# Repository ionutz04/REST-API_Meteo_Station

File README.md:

# 🌦️ SHT21 REST API - IoT Weather Monitoring Station

**Collaborators:** Ionescu Ionut

---

## 📝 General Description

This project implements a robust **IoT Weather Monitoring Station** designed for high-accuracy environmental data acquisition. The system is built around an **ESP32 microcontroller** running FreeRTOS (via ESP-IDF) and integrates with a local **NVIDIA Jetson Nano** gateway for data processing and storage.

### System Architecture
- **Edge Node (ESP32):** Collects sensor data via I²C, ADC, and Interrupt Service Routines (ISR).
- **Communication:** Secure HTTPS transmission (Ad-Hoc WiFi) to a Flask REST API.
- **Backend:** Redis TimeSeries database for high-speed storage.
- **Visualization:** Real-time Grafana dashboards.

### 🔑 Key Features
| Feature | Description |
| :--- | :--- |
| **Real-time Acquisition** | Low-latency polling of temperature, humidity, pressure, and wind metrics. |
| **Secure Transport** | JWT-authenticated HTTPS transmission between edge and gateway. |
| **Data Integrity** | Time-series storage with automatic aggregation and persistence. |
| **Visualization** | Custom Grafana dashboards for instant monitoring. |
| **Export Capability** | CSV data export for offline meteorological analysis. |

---

## 🧾 BOM (Bill Of Materials)

| # | Component | Quantity | Description | Interface/Notes |
|:-:|:---|:-:|:---|:---|
| 1 | **ESP32 DevKit** | 1 | ESP32-WROOM-32 Development Board | Main Controller |
| 2 | **SHT21** | 1 | Digital Temp & Humidity Sensor | I²C (0x40) |
| 3 | **MS5611** | 1 | Barometric Pressure Sensor | I²C |
| 4 | **GP2Y Series** | 1 | Optical Dust Sensor (e.g., GP2Y1014AU0F) | Analog + LED Pulse |
| 5 | **SparkFun Weather Meter** | 1 | [SEN-15901](https://www.sparkfun.com/products/15901) Kit | Wind/Rain Assembly |
| 6 | **10kΩ Resistors** | 2 | 1/4W Resistors | Voltage Divider (Wind Vane) |
| 7 | **Nvidia Jetson Nano** | 1 | Orin / 8GB Model | Gateway & ML Server |
| 8 | **Power Supply** | 1 | 5V DC Source | Reliable supply for ESP32 |
| 9 | **Enclosure** | 1 | IP65/Weatherproof Box | Outdoor deployment |

### 🔌 Sensor Pinout Configuration
| Sensor | Signal Type | ESP32 Pin | Logic |
| :--- | :--- | :--- | :--- |
| **Anemometer** | Digital (Pulse) | `GPIO32` | ISR (Falling Edge) |
| **Wind Vane** | Analog (ADC) | `GPIO36` | Voltage Divider Network |
| **Rain Gauge** | Digital (Pulse) | `GPIO33` | ISR (Debounced) |
| **GP2Y1014**| LED - Digital ; photodetector - Analog | `GPIO34` | The LED toggles on 20 $\mu s$ and the analog pin reads the time interval between "the start" of the dust particle and the end of it  |
| **SHT21** | I²C | `SDA/SCL` on address `0x40` | Polling Task |
| **MS5611** | I²C | `SDA/SCL` on address `0x70` | Polling Task |
---

## 🧐 Technical FAQ

### Q1: What is the system boundary?
The system encompasses the **ESP32 firmware** (edge) and the **Jetson Nano microservices** (gateway). External dependencies are strictly limited to standard libraries (ESP-IDF, Flask, Redis, Grafana). The REST API implements a custom AAA (Authentication, Authorization, Accounting) model inspired by industry standards.

### Q2: Where does the intelligence live?
Decision-making is centralized on the **Local Server Gateway (Jetson Nano Orin)**. This device hosts the containerized microservices and executes forecasting algorithms. The ESP32 acts as a "dumb" reliable data pipe.

### Q3: What were the primary engineering challenges?
1.  **State Management:** Implementing Non-Deterministic Finite Automata logic for the REST API to handle MySQL cursors, Redis connections, and JWT verification simultaneously without race conditions.
2.  **Firmware Stability:** Early versions suffered from frequent disconnects due to blocking MySQL cursors freezing the Docker container. Transitioning to a Gunicorn worker model and an asynchronous automata architecture resolved this.

### Q4: Why is this not just a tutorial?
This is not a copy-paste hobby project. It addresses a specific engineering constraint: **"How to build a meteorological station with low latency but high forecasting accuracy."** The architecture prioritizes data integrity and system autonomy over simplicity.

---

## 📅 Development Timeline

### Phase 1: Prototyping (Arduino Framework)
* **20 Dec 2025 - 03 Jan 2026:** Project initiation. Initial implementation using Arduino framework for ESP32 and Flask for the backend, implementation which turned up to be very unstable and very unefficient in battery life for the MCU.
* **14 Jan 2026:** Hardware arrival (SparkFun Meter Kit). Beta testing begins, transfering the initial flask web app to a more production ready system, using multi-threaded solution like gunicorn, sepparating each route task to every worker.
* **14 Jan 2026 - 18 Jan 2026:** Completion of the Arduino-based prototype. Data gathering initiated for initial model training.

### Phase 2: Refactoring (ESP-IDF Migration)
* **20 Jan 2026:** **Critical Decision:** The Arduino framework proved resource-heavy and inefficient. Decision made to migrate to **ESP-IDF** (Espressif IoT Development Framework). The inefficency was found when it was tring a more battery oriented firmware, the deep sleep implementation on the ESP32 turning out to be full of bugs. (At the end of the day "At the end of the day, Arduino is like training wheels on a bicycle, after you learn to walk, it just hinders you." 😎)

* **22 Jan 2026 - 01 Feb 2026:** **Learing ESP-IDF Stage.**
    * Learned FreeRTOS task/queue management.
    * Wrote custom $I^2C$ driver for SHT21.
    * Migrated from simple loops to multi-tasking architecture.

### Phase 3: Production Release
* **04 Feb 2026:** **R&D Complete.**
    * Final firmware deployed using ESP-IDF.
    * **Architecture:** Dedicated FreeRTOS tasks for each sensor (SHT21, MS5611, GP2Y) and even for the meter kit sensors, like anemometer, rain gauge and Wind Vane. For interrupt-dependent sensors, like rain gauge and anemometer, it was implemented a queue for each IRS-Task link, being a solution of debounce or other problems which can be induced by noise.
    * **Connectivity:** Migrated to Ad-Hoc WiFi network (Jetson as AP, ESP32 as STA) for isolated security because the real Meteo Stations are needed in isolated places, and the possibility of not having a wireless connection in order to connect the ESP32 to JON.

### 🚀 Future Roadmap
* Using the LTSM network it is planed for the final version for the Project presentation to be configured for forcasting
* Also for this presentation, it is planed to create a custom dashboard for the time series graphs, also being able to have access to the forcasting tab.

### 📡 PCB design

* 7th Febrary 2026: Getting done the first prototipe board for this meter kit.
For now, the state in which stays the custom PCB which it was designed for this project is close to be the final one, the only modifications that are needed are regaring the footprint of the esp32 and sensors like SHT21, MS5611. The GP2Y will be soldered on the board using a JCTC connector, solderd directly on board.

* 1st March 2026: Second prototipe board for the meter kit:
   Right now, this is the state in which the project is:

   - 3D view:

   - Schematic:

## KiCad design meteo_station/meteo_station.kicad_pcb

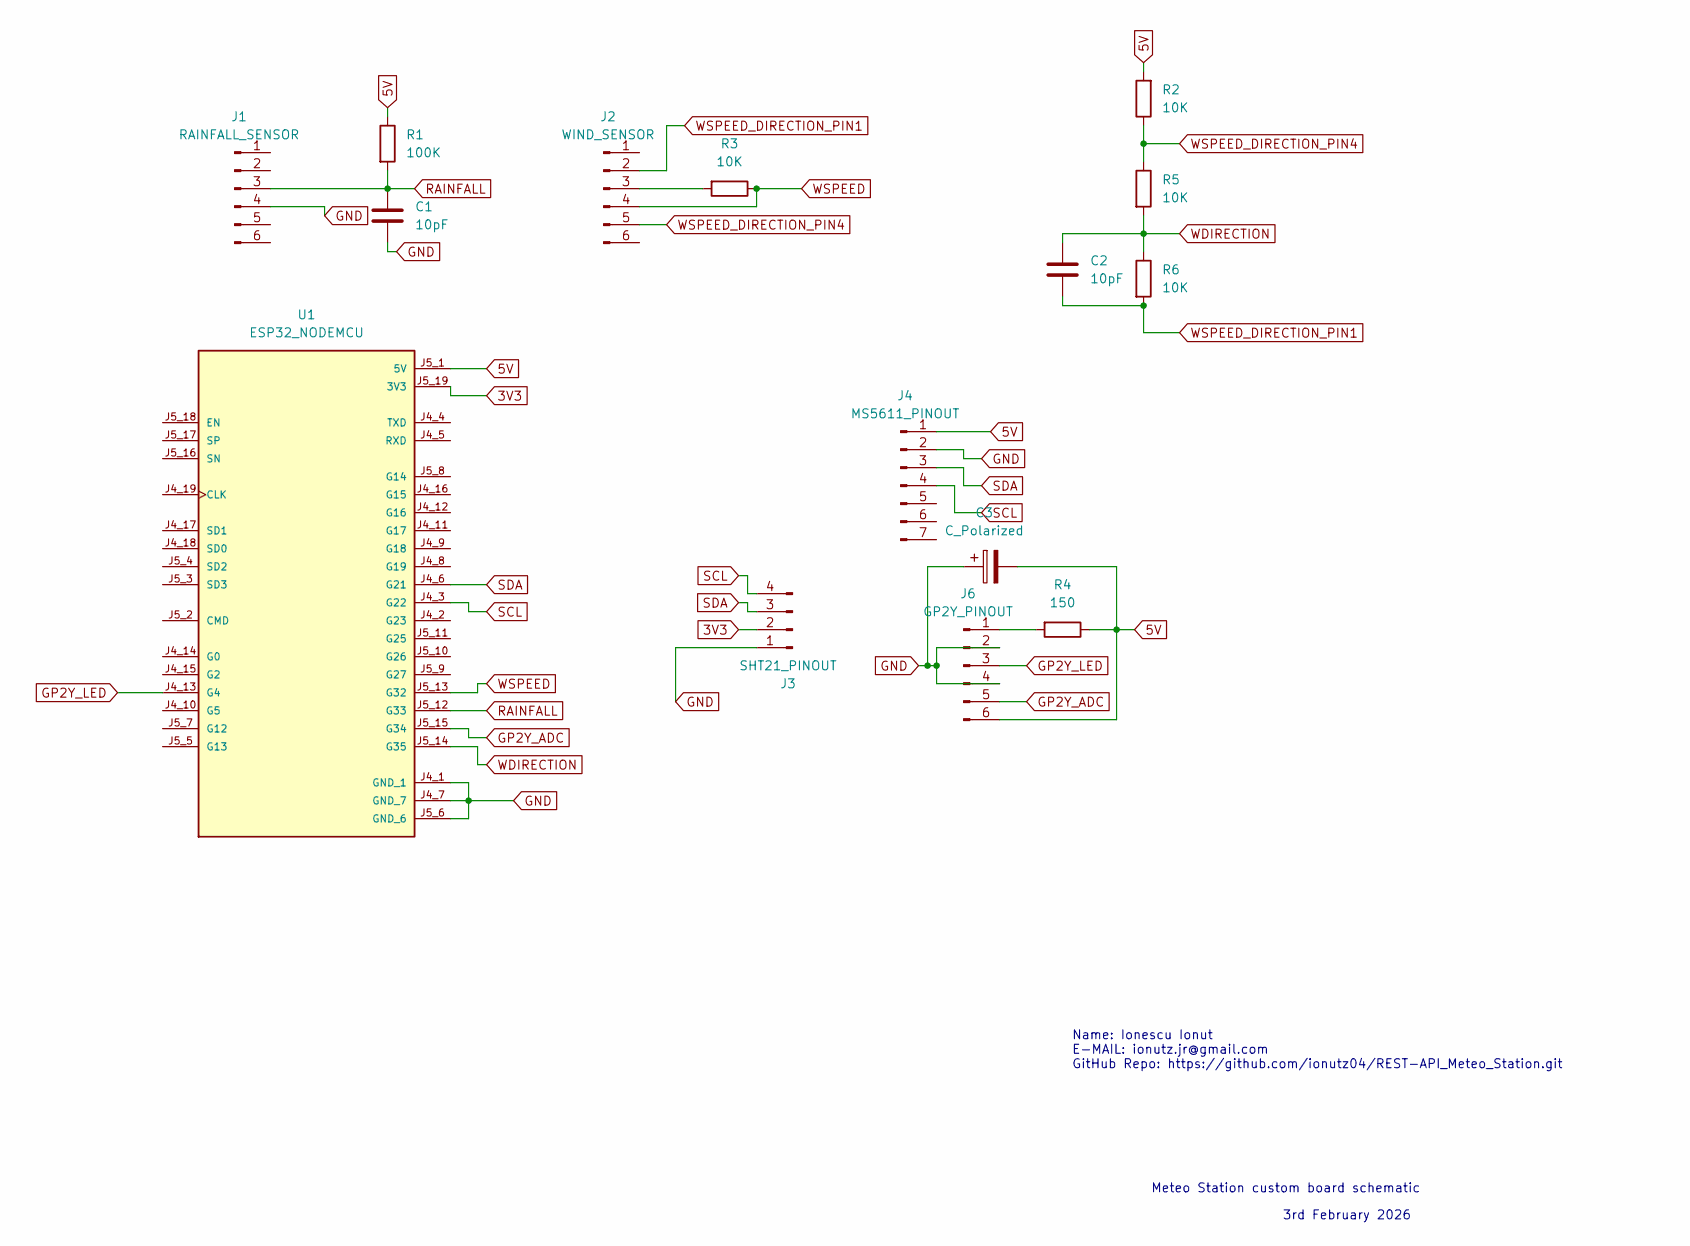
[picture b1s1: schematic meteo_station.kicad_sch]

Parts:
C1, C2: 10pF; C_1206_3216Metric_Pad1.33x1.80mm_HandSolder
C3: C_Polarized; CP_Elec_3x5.3
J1: RAINFALL_SENSOR; PinHeader_1x06_P2.54mm_Vertical
J2: WIND_SENSOR; PinHeader_1x06_P2.54mm_Vertical
J3: SHT21_PINOUT; PinHeader_1x04_P2.54mm_Vertical
J4: MS5611_PINOUT; PinHeader_1x07_P2.54mm_Vertical
J6: GP2Y_PINOUT; PinHeader_1x06_P2.54mm_Vertical
R1: 100K; R_1206_3216Metric_Pad1.30x1.75mm_HandSolder
R2, R3, R5, R6: 10K; R_1206_3216Metric_Pad1.30x1.75mm_HandSolder
R4: 150; R_1206_3216Metric_Pad1.30x1.75mm_HandSolder
U1: ESP32_NODEMCU; MODULE_ESP32_NODEMCU

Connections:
3V3: J3.2, U1.J5_19 (3V3)
5V: C3.2, J4.1, J6.6, R1.1, R2.2, R4.1, U1.J5_1 (5V)
GND: C1.2, C3.1, J1.4, J3.1, J4.2, J6.2, J6.4, U1.J4_1 (GND_1), U1.J4_7 (GND_7), U1.J5_6 (GND_6)
GP2Y_ADC: J6.5, U1.J5_15 (G34)
GP2Y_LED: J6.3, U1.J4_13 (G4)
unnamed: J2.3, R3.2
unnamed: J6.1, R4.2
RAINFALL: C1.1, J1.3, R1.2, U1.J5_12 (G33)
SCL: J3.4, J4.4, U1.J4_3 (G22)
SDA: J3.3, J4.3, U1.J4_6 (G21)
WDIRECTION: C2.1, R5.2, R6.1, U1.J5_14 (G35)
WSPEED: J2.4, R3.1, U1.J5_13 (G32)
WSPEED_DIRECTION_PIN1: C2.2, J2.2, R6.2
WSPEED_DIRECTION_PIN4: J2.5, R2.1, R5.1

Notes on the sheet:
3rd February 2026
Name: Ionescu Ionut E-MAIL: ionutz.jr@gmail.com GitHub Repo: https://github.com/ionutz04/REST-API_Meteo_Station.git
Meteo Station custom board schematic

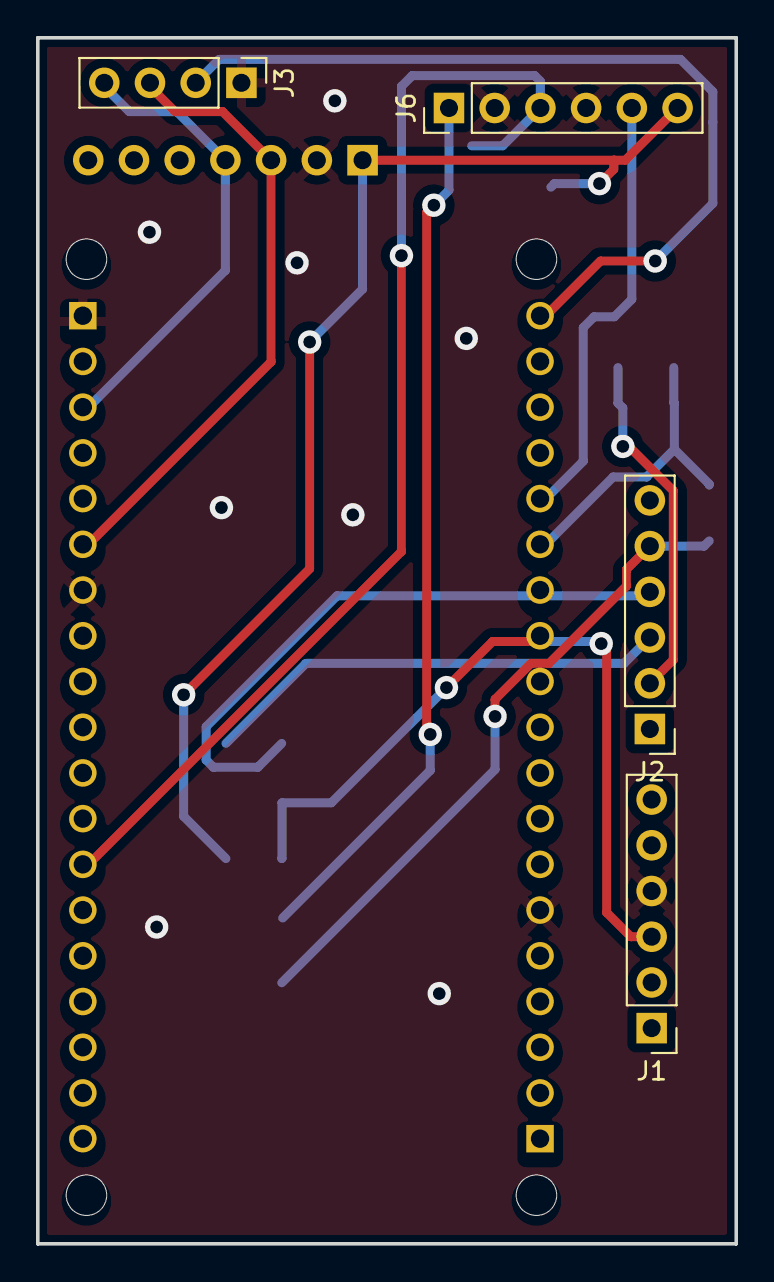
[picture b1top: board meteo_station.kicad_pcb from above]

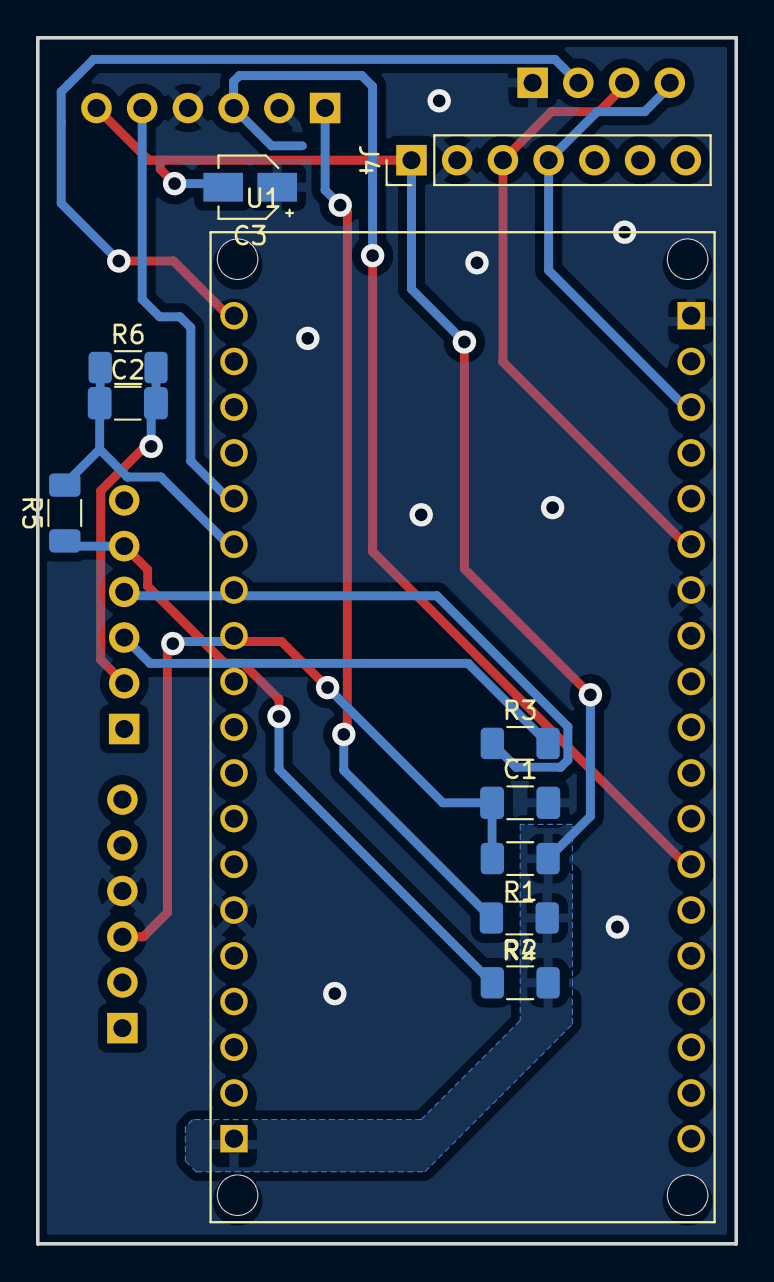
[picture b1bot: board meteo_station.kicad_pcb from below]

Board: 2 copper layers, 38.8 x 67.0 mm, 15 parts (11 on the bottom side), 14 nets.

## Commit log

2026-01-01 Final commit for esp32-jetson1 architecture system based on REST API
2026-01-05 addition of snmp interrogation system using multi-threaded subsystem python application
2026-01-07 Final commit for first presentation of the year.
2026-01-07 Small changes over README.md
2026-01-08 Add collaborators to README
2026-01-08 Update README with collaborators information
    Add collaborators section to README
2026-01-11 Final update over the reenforced architecture, with whitelist and blacklist database, and production rated gunicorn upgrade over the REST API server.
2026-01-19 Update on README.md for Robotics project
2026-02-04 Upgraded implementation of the REST-API using only ESP-IDF as framework for very efficient task management. Also, commiting the implementations for the sensors MS5611 and GP2Y1014, one being the pres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
2026-02-06 Final commit before the Robotics Presentation
2026-02-06 Addition of the kicad project
2026-03-01 MeteoStationV2 stable
2026-03-02 First forcasting comit
2026-03-02 first forcasting chart for 24Hrs
2026-04-14 Updates for grafana server and fixes overall.
2026-04-16 Initial implementation of Multilayer LSTM for forecasting task
2026-04-21 modifications over prediction algorihm
2026-04-21 midification on .gitignore
2026-04-22 addition of a new version of analysis
2026-04-24 Camera-monitor update

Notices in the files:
README.md:
License: MIT
